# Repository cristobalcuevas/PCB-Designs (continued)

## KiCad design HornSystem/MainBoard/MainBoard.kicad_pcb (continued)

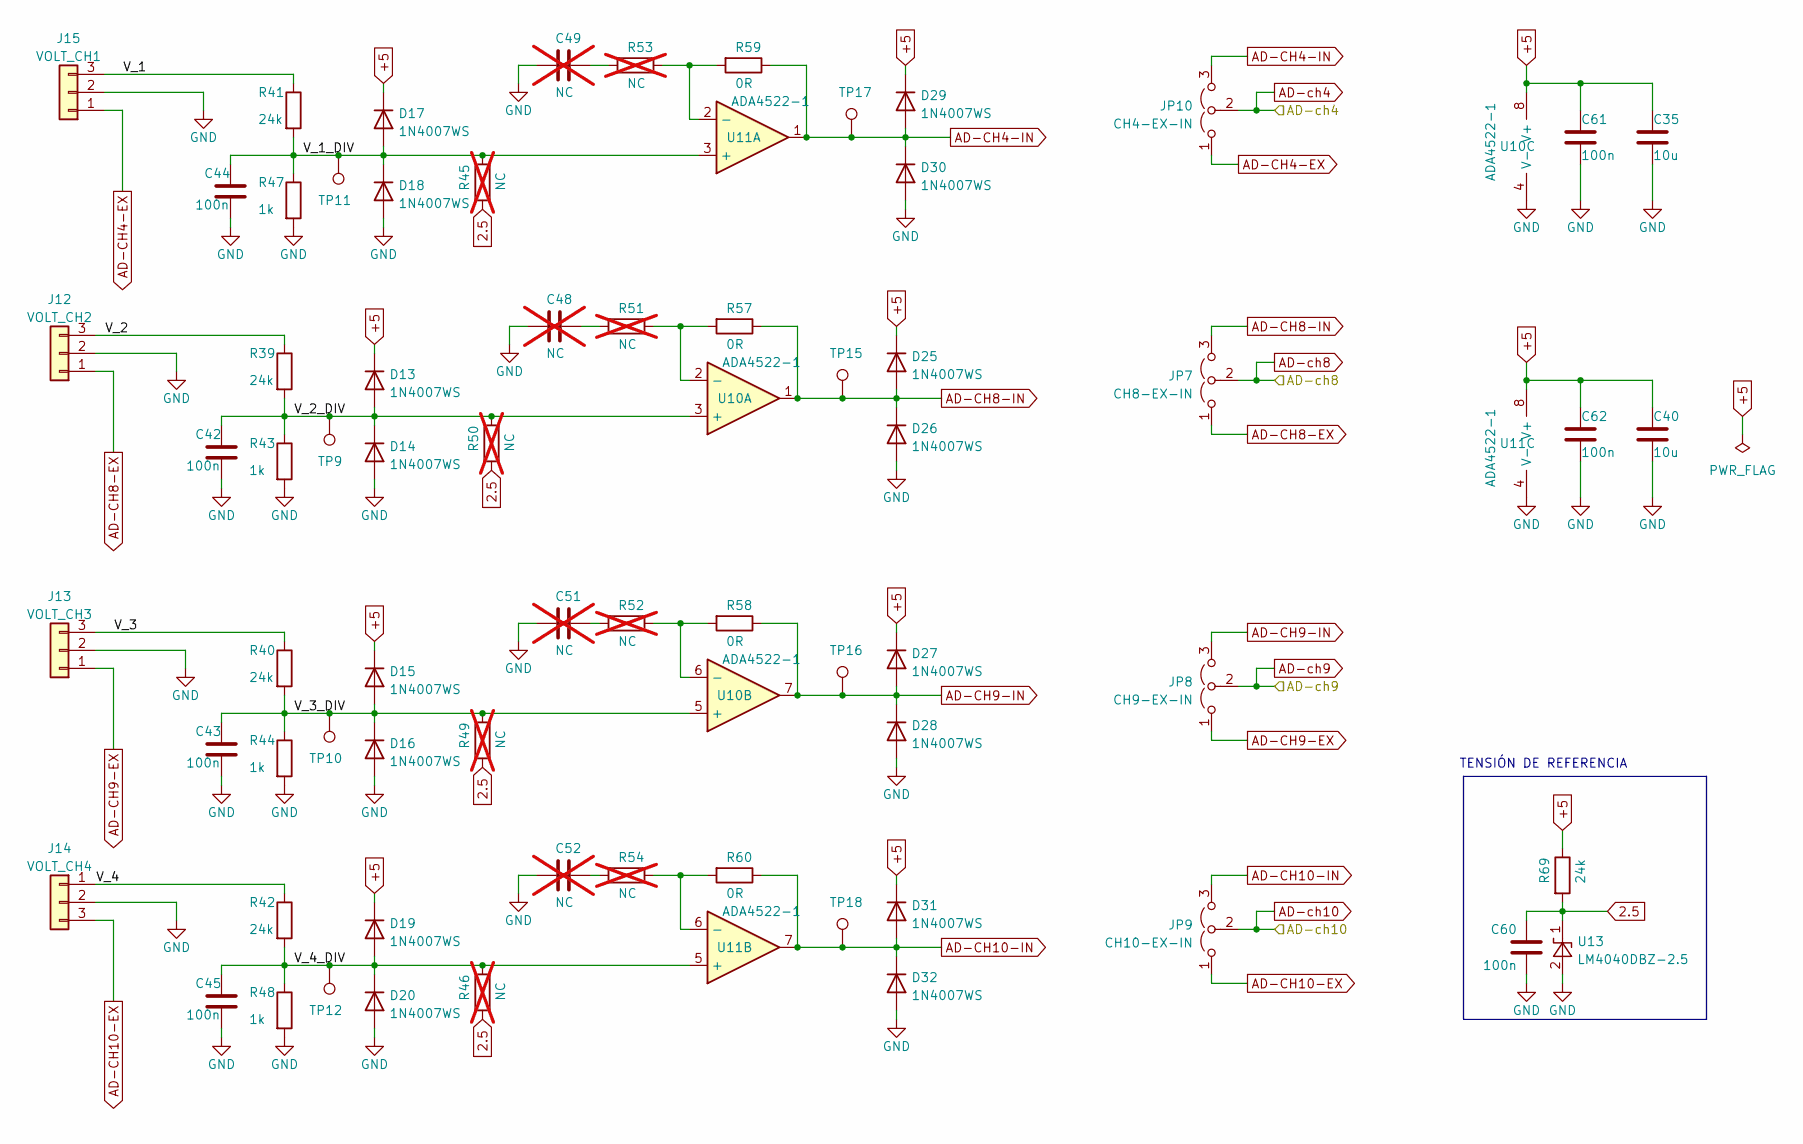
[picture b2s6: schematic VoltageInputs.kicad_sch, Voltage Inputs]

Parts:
C35, C40: 10u; C_0805_2012Metric; JLCPCB Part C380331
C42, C43, C44, C45, C60, C61, C62: 100n; C_0805_2012Metric; JLCPCB Part C710457
C48, C49, C51, C52: NC; C_0805_2012Metric; not fitted
D13, D14, D15, D16, D17, D18, D19, D20, D25, D26, D27, D28, D29, D30, D31, D32: 1N4007WS; D_SOD-323; JLCPCB Part C193404
J12: VOLT_CH2; PinHeader_1x03_P2.54mm_Vertical
J13: VOLT_CH3; PinHeader_1x03_P2.54mm_Vertical
J14: VOLT_CH4; PinHeader_1x03_P2.54mm_Vertical
J15: VOLT_CH1; PinHeader_1x03_P2.54mm_Vertical
JP7: CH8-EX-IN; SolderJumper-3_P1.3mm_Open_RoundedPad1.0x1.5mm_NumberLabels
JP8: CH9-EX-IN; SolderJumper-3_P1.3mm_Open_RoundedPad1.0x1.5mm_NumberLabels
JP9: CH10-EX-IN; SolderJumper-3_P1.3mm_Open_RoundedPad1.0x1.5mm_NumberLabels
JP10: CH4-EX-IN; SolderJumper-3_P1.3mm_Open_RoundedPad1.0x1.5mm_NumberLabels
R39, R40, R41, R42, R69: 24k; R_0805_2012Metric; JLCPCB Part C286604
R43, R44, R47, R48: 1k; R_0805_2012Metric; JLCPCB Part C335229
R45, R46, R49, R50, R51, R52, R53, R54: NC; R_0805_2012Metric; not fitted
R57, R58, R59, R60: 0R; R_0805_2012Metric; JLCPCB Part C2907288
TP9, TP10, TP11, TP12, TP15, TP16, TP17, TP18: TestPoint; TestPoint_Pad_D1.0mm
U10, U11: ADA4522-1; MSOP-8_3x3mm_P0.65mm; JLCPCB Part C127898
U13: LM4040DBZ-2.5; SOT-23; JLCPCB Part C131939

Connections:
2.5: C60.2, R45.2, R46.2, R49.2, R50.2, R69.2, U13.1 (K)
+5: C35.1, C40.1, C61.1, C62.1, D13.1 (K), D15.1 (K), D17.1 (K), D19.1 (K), D25.1 (K), D27.1 (K), D29.1 (K), D31.1 (K), R69.1, U10.8 (V+), U11.8 (V+); also elsewhere on the board
/VoltageInputs/V_1: J15.3, R41.1
/VoltageInputs/V_1_DIV: C44.1, D17.2 (A), D18.1 (K), R41.2, R45.1, R47.1, TP11.1, U11.3 (+)
/VoltageInputs/V_2: J12.3, R39.1
/VoltageInputs/V_2_DIV: C42.1, D13.2 (A), D14.1 (K), R39.2, R43.1, R50.1, TP9.1, U10.3 (+)
/VoltageInputs/V_3: J13.3, R40.1
/VoltageInputs/V_3_DIV: C43.1, D15.2 (A), D16.1 (K), R40.2, R44.1, R49.1, TP10.1, U10.5 (+)
/VoltageInputs/V_4: J14.1, R42.1
/VoltageInputs/V_4_DIV: C45.1, D19.2 (A), D20.1 (K), R42.2, R46.1, R48.1, TP12.1, U11.5 (+)
AD-CH4-EX: J15.1, JP10.1 (A)
AD-CH4-IN: D29.2 (A), D30.1 (K), JP10.3 (B), R59.1, TP17.1, U11.1
AD-CH8-EX: J12.1, JP7.1 (A)
AD-CH8-IN: D25.2 (A), D26.1 (K), JP7.3 (B), R57.1, TP15.1, U10.1
AD-CH9-EX: J13.1, JP8.1 (A)
AD-CH9-IN: D27.2 (A), D28.1 (K), JP8.3 (B), R58.1, TP16.1, U10.7
AD-CH10-EX: J14.3, JP9.1 (A)
AD-CH10-IN: D31.2 (A), D32.1 (K), JP9.3 (B), R60.1, TP18.1, U11.7
AD-ch4: JP10.2 (C); also elsewhere on the board
AD-ch8: JP7.2 (C); also elsewhere on the board
AD-ch9: JP8.2 (C); also elsewhere on the board
AD-ch10: JP9.2 (C); also elsewhere on the board
GND: C35.2, C40.2, C42.2, C43.2, C44.2, C45.2, C48.2, C49.2, C51.2, C52.2, C60.1, C61.2, C62.2, D14.2 (A), D16.2 (A), D18.2 (A), D20.2 (A), D26.2 (A), D28.2 (A), D30.2 (A), D32.2 (A), J12.2, J13.2, J14.2, J15.2, R43.2, R44.2, R47.2, R48.2, U10.4 (V-), U11.4 (V-), U13.2 (A); also elsewhere on the board
unnamed: C48.1, R51.2
unnamed: C49.1, R53.2
unnamed: C51.1, R52.2
unnamed: C52.1, R54.2
unnamed: R51.1, R57.2, U10.2 (-)
unnamed: R52.1, R58.2, U10.6 (-)
unnamed: R53.1, R59.2, U11.2 (-)
unnamed: R54.1, R60.2, U11.6 (-)

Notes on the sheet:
TENSIÓN DE REFERENCIA

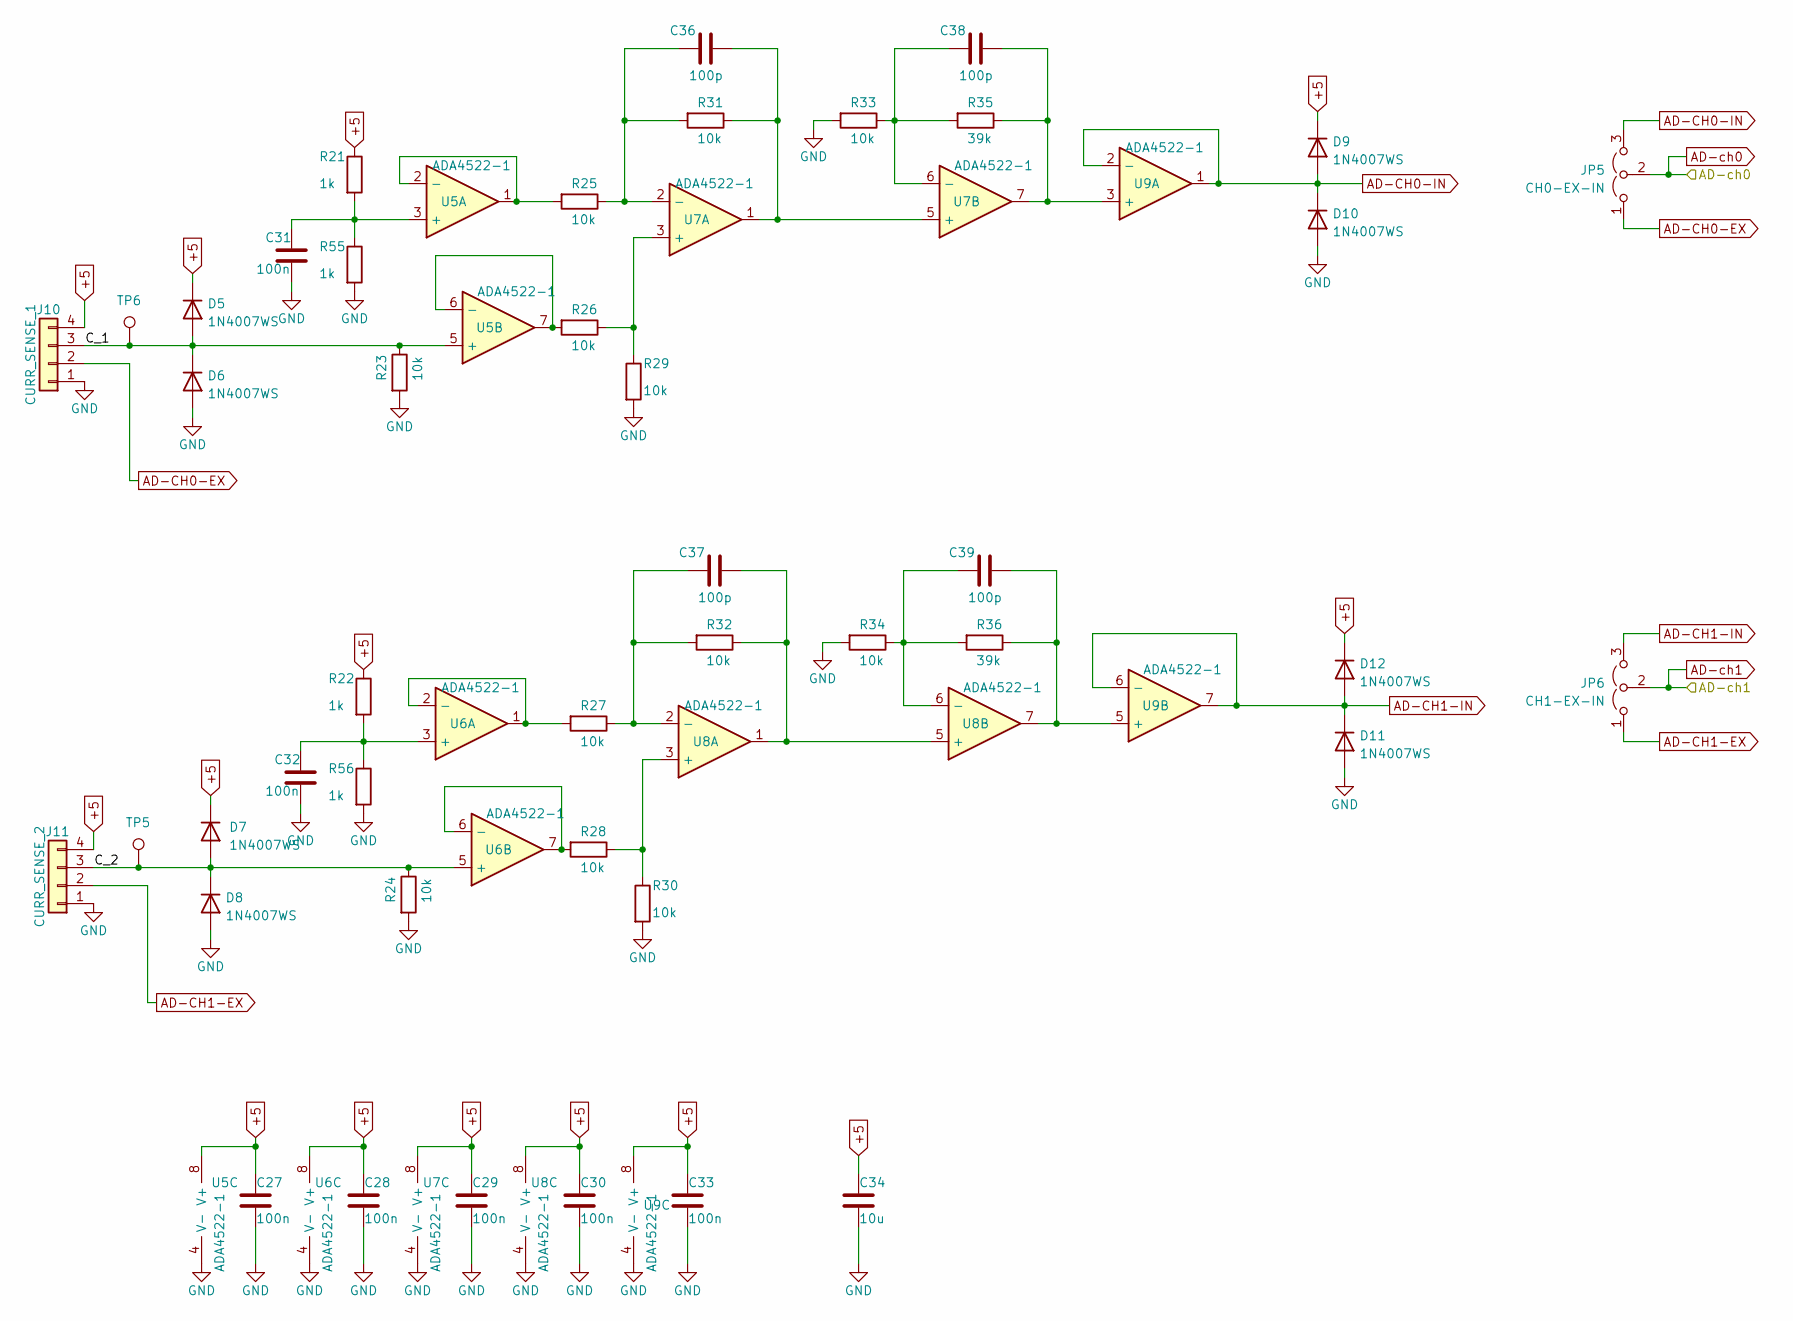
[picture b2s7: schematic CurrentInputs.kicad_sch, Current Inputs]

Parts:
C27, C28, C29, C30, C31, C32, C33: 100n; C_0805_2012Metric; JLCPCB Part C710457
C34: 10u; C_0805_2012Metric; JLCPCB Part C380331
C36, C37, C38, C39: 100p; C_0805_2012Metric; JLCPCB Part C2691714
D5, D6, D7, D8, D9, D10, D11, D12: 1N4007WS; D_SOD-323; JLCPCB Part C193404
J10: CURR_SENSE_1; PinHeader_1x04_P2.54mm_Vertical
J11: CURR_SENSE_2; PinHeader_1x04_P2.54mm_Vertical
JP5: CH0-EX-IN; SolderJumper-3_P1.3mm_Open_RoundedPad1.0x1.5mm_NumberLabels
JP6: CH1-EX-IN; SolderJumper-3_P1.3mm_Open_RoundedPad1.0x1.5mm_NumberLabels
R21, R22, R55, R56: 1k; R_0805_2012Metric; JLCPCB Part C335229
R23, R24, R25, R26, R27, R28, R29, R30, R31, R32, R33, R34: 10k; R_0805_2012Metric; JLCPCB Part C212284
R35, R36: 39k; R_0805_2012Metric; JLCPCB Part C139877
TP5, TP6: TestPoint; TestPoint_Pad_D1.0mm
U5, U6, U7, U8, U9: ADA4522-1; MSOP-8_3x3mm_P0.65mm; JLCPCB Part C127898

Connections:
+5: C27.1, C28.1, C29.1, C30.1, C33.1, C34.1, D5.1 (K), D7.1 (K), D9.1 (K), D12.1 (K), J10.4, J11.4, R21.1, R22.1, U5.8 (V+), U6.8 (V+), U7.8 (V+), U8.8 (V+), U9.8 (V+); also elsewhere on the board
/CurrentInputs/C_1: D5.2 (A), D6.1 (K), J10.3, R23.1, TP6.1, U5.5 (+)
/CurrentInputs/C_2: D7.2 (A), D8.1 (K), J11.3, R24.1, TP5.1, U6.5 (+)
AD-CH0-EX: J10.2, JP5.1 (A)
AD-CH0-IN: D9.2 (A), D10.1 (K), JP5.3 (B), U9.1, U9.2 (-)
AD-CH1-EX: J11.2, JP6.1 (A)
AD-CH1-IN: D11.1 (K), D12.2 (A), JP6.3 (B), U9.6 (-), U9.7
AD-ch0: JP5.2 (C); also elsewhere on the board
AD-ch1: JP6.2 (C); also elsewhere on the board
GND: C27.2, C28.2, C29.2, C30.2, C31.2, C32.2, C33.2, C34.2, D6.2 (A), D8.2 (A), D10.2 (A), D11.2 (A), J10.1, J11.1, R23.2, R24.2, R29.2, R30.2, R33.2, R34.2, R55.2, R56.2, U5.4 (V-), U6.4 (V-), U7.4 (V-), U8.4 (V-), U9.4 (V-); also elsewhere on the board
unnamed: C31.1, R21.2, R55.1, U5.3 (+)
unnamed: R25.2, U5.1, U5.2 (-)
unnamed: R26.2, U5.6 (-), U5.7
unnamed: C32.1, R22.2, R56.1, U6.3 (+)
unnamed: R27.2, U6.1, U6.2 (-)
unnamed: R28.2, U6.6 (-), U6.7
unnamed: R26.1, R29.1, U7.3 (+)
unnamed: C36.1, R25.1, R31.2, U7.2 (-)
unnamed: C36.2, R31.1, U7.1, U7.5 (+)
unnamed: C38.1, R33.1, R35.2, U7.6 (-)
unnamed: R28.1, R30.1, U8.3 (+)
unnamed: C37.1, R27.1, R32.2, U8.2 (-)
unnamed: C37.2, R32.1, U8.1, U8.5 (+)
unnamed: C39.1, R34.1, R36.2, U8.6 (-)
unnamed: C38.2, R35.1, U7.7, U9.3 (+)
unnamed: C39.2, R36.1, U8.7, U9.5 (+)

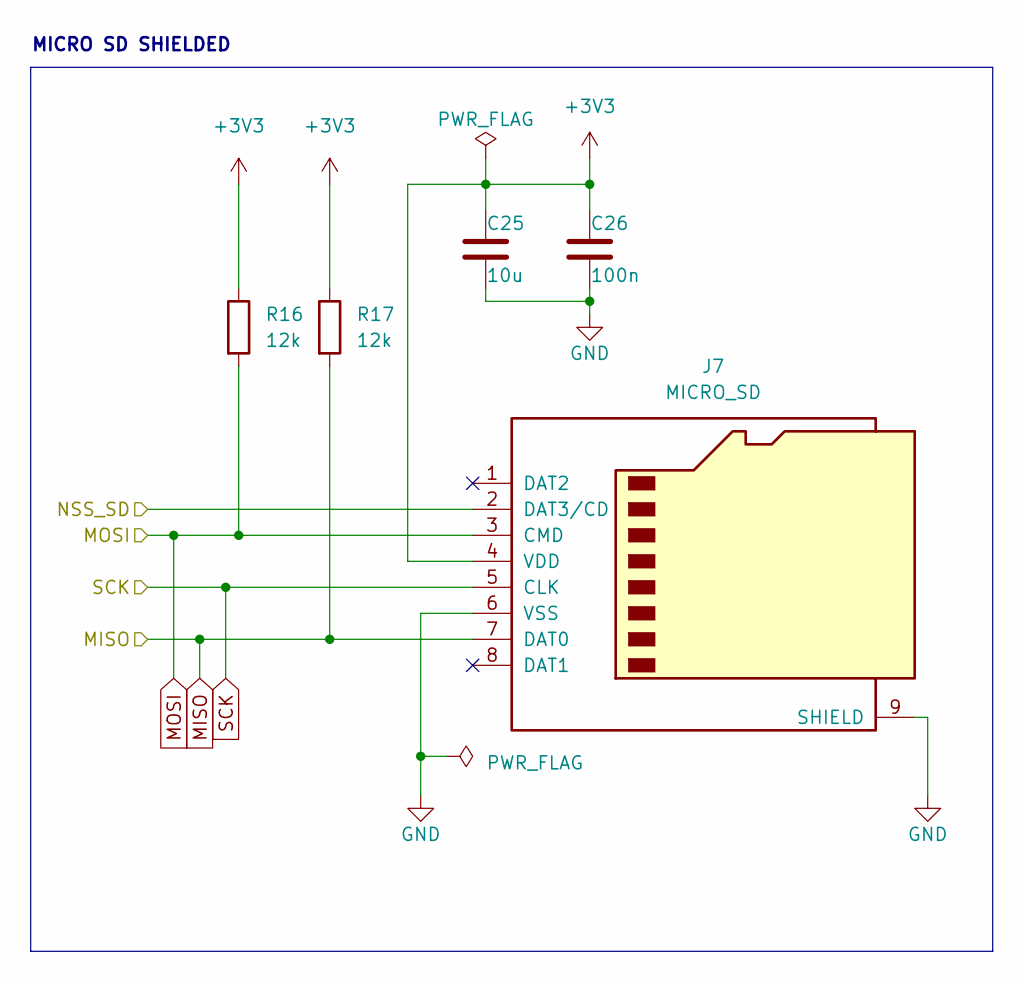
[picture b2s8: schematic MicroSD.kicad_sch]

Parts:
C25: 10u; C_0805_2012Metric; JLCPCB Part C380331
C26: 100n; C_0805_2012Metric; JLCPCB Part C710457
J7: MICRO_SD; microSD_HC_Molex_104031-0811; JLCPCB Part C585350
R16, R17: 12k; R_0805_2012Metric; JLCPCB Part C114556

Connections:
+3V3: C25.1, C26.1, J7.4 (VDD), R16.1, R17.1; also elsewhere on the board
/MCU/NSS_SD: J7.2 (DAT3/CD); also elsewhere on the board
GND: C25.2, C26.2, J7.6 (VSS), J7.9 (SHIELD); also elsewhere on the board
MISO: J7.7 (DAT0), R17.2; also elsewhere on the board
MOSI: J7.3 (CMD), R16.2; also elsewhere on the board
SCK: J7.5 (CLK); also elsewhere on the board

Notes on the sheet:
MICRO SD SHIELDED

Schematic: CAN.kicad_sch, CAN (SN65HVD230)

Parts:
C15: 100n; C_0805_2012Metric; JLCPCB Part C710457
J8: CAN_MODE; PinHeader_1x03_P2.54mm_Vertical
J20: CAN; PinHeader_1x02_P2.54mm_Vertical
R8: 20k; R_0805_2012Metric; JLCPCB Part C136576
R18: 0R; R_0805_2012Metric; JLCPCB Part C2907288
R19: 120R; R_0805_2012Metric; JLCPCB Part C912585
U12: SN65HVD230; SOIC-8_3.9x4.9mm_P1.27mm; JLCPCB Part C12084

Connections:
+3V3: C15.1, R18.2, U12.3 (VCC); also elsewhere on the board
/CAN/CAN_H: J20.1, R19.1, U12.7 (CANH)
/CAN/CAN_L: J20.2, R19.2, U12.6 (CANL)
/CAN/RS: J8.2, R8.1, U12.8 (Rs)
CAN_RX: U12.4 (R); also elsewhere on the board
CAN_TX: U12.1 (D); also elsewhere on the board
GND: C15.2, J8.3, R8.2, U12.2 (GND); also elsewhere on the board
unnamed: J8.1, R18.1

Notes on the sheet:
CAN

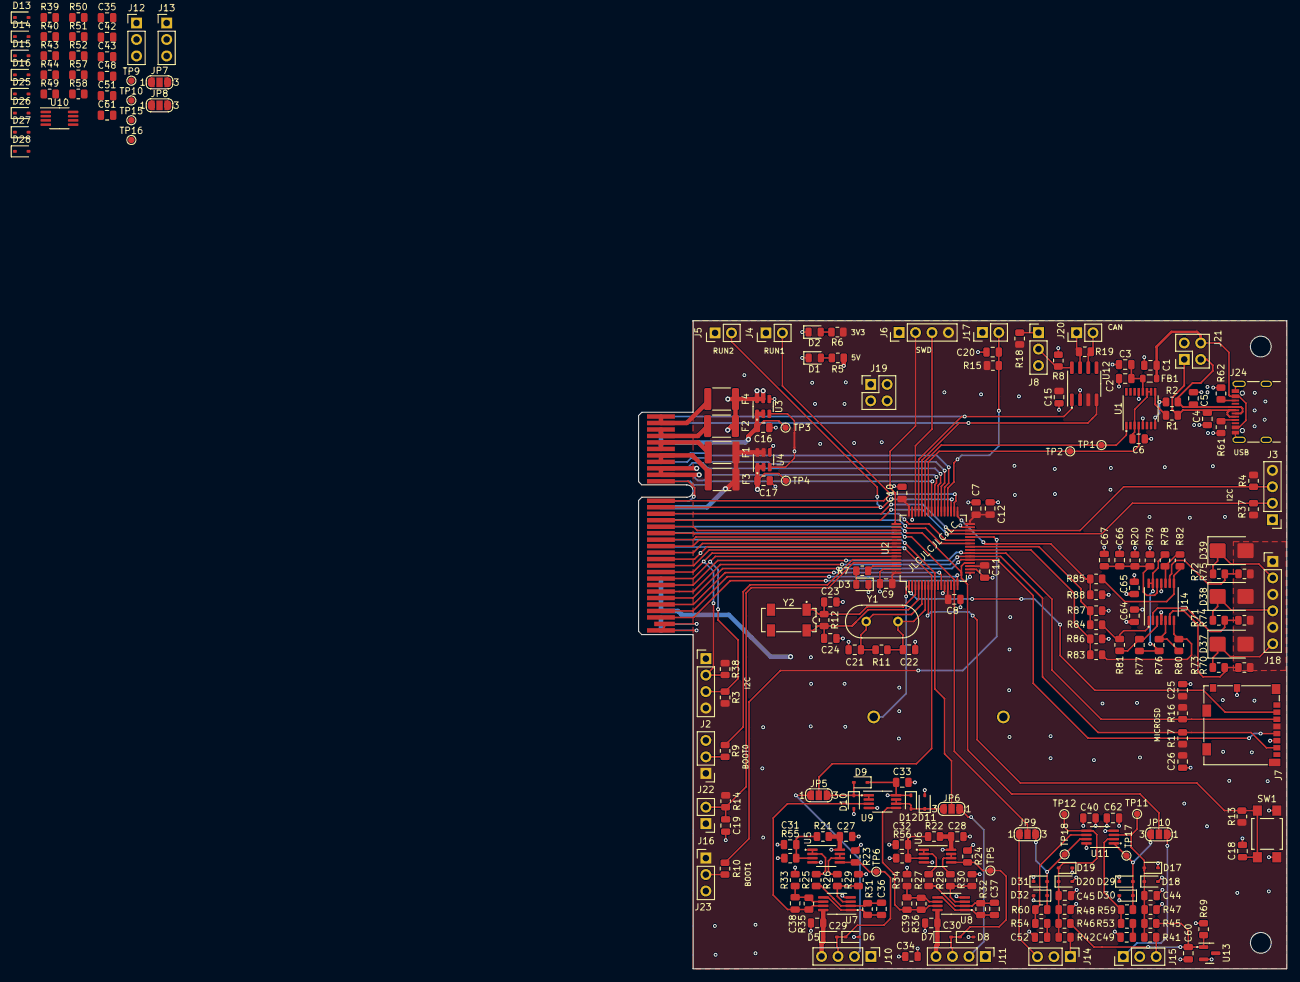
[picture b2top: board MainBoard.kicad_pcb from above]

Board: 4 copper layers, 100.0 x 100.0 mm, 233 parts (1 on the bottom side), 140 nets.

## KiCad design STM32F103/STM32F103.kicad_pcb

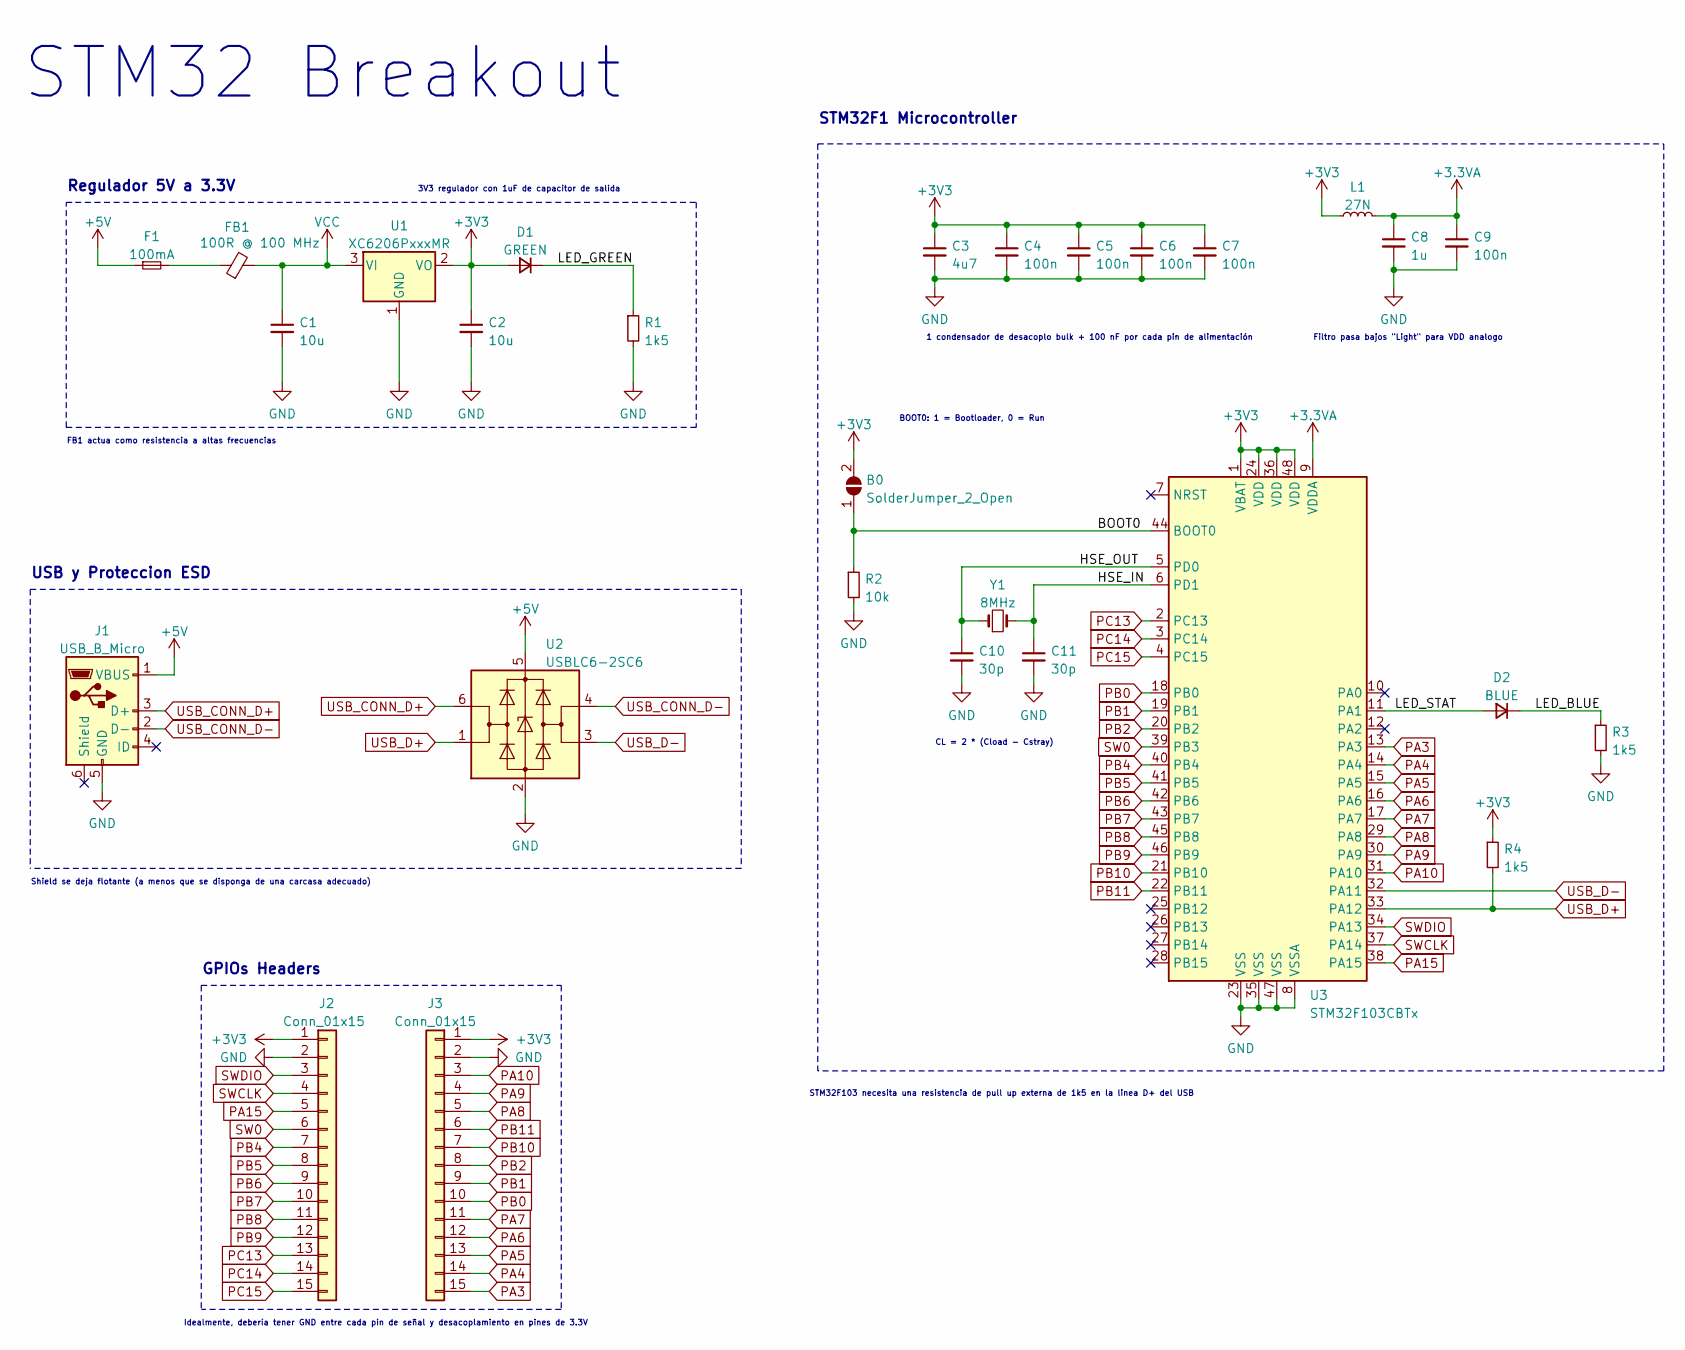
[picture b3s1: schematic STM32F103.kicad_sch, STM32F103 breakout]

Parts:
B0: SolderJumper_2_Open; SolderJumper-2_P1.3mm_Open_Pad1.0x1.5mm
C1, C2: 10u; C_0603_1608Metric
C3: 4u7; C_0603_1608Metric
C4, C5, C6, C7, C9: 100n; C_0402_1005Metric
C8: 1u; C_0402_1005Metric
C10, C11: 30p; C_0402_1005Metric
D1: GREEN; LED_0603_1608Metric
D2: BLUE; LED_0603_1608Metric
F1: 100mA; Fuse_0603_1608Metric
FB1: 100R @ 100 MHz; L_0805_2012Metric
J1: USB_B_Micro; USB_Micro-B_Wuerth_629105150521
J2, J3: Conn_01x15; PinHeader_1x15_P2.54mm_Vertical
L1: 27N; L_0402_1005Metric
R1, R3: 1k5; R_0603_1608Metric
R2: 10k; R_0402_1005Metric
R4: 1k5; R_0402_1005Metric
U1: XC6206PxxxMR; SOT-23
U2: USBLC6-2SC6; SOT-23-6
U3: STM32F103CBTx; LQFP-48_7x7mm_P0.5mm
Y1: 8MHz; Crystal_SMD_5032-2Pin_5.0x3.2mm

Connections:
+3.3VA: C8.1, C9.1, L1.2, U3.9 (VDDA)
+3V3: B0.2 (B), C2.1, C3.1, C4.1, C5.1, C6.1, C7.1, D1.2 (A), J2.1, J3.1, L1.1, R4.1, U1.2 (VO), U3.1 (VBAT), U3.24 (VDD), U3.36 (VDD), U3.48 (VDD)
+5V: F1.1, J1.1 (VBUS), U2.5 (VBUS)
/BOOT0: B0.1 (A), R2.1, U3.44 (BOOT0)
/HSE_IN: C11.1, U3.6 (PD1), Y1.2
/HSE_OUT: C10.1, U3.5 (PD0), Y1.1
/LED_BLUE: D2.1 (K), R3.1
/LED_GREEN: D1.1 (K), R1.1
/LED_STAT: D2.2 (A), U3.11 (PA1)
GND: C1.2, C2.2, C3.2, C4.2, C5.2, C6.2, C7.2, C8.2, C9.2, C10.2, C11.2, J1.5 (GND), J2.2, J3.2, R1.2, R2.2, R3.2, U1.1 (GND), U2.2 (GND), U3.8 (VSSA), U3.23 (VSS), U3.35 (VSS), U3.47 (VSS)
unnamed: F1.2, FB1.1
PA3: J3.15, U3.13 (PA3)
PA4: J3.14, U3.14 (PA4)
PA5: J3.13, U3.15 (PA5)
PA6: J3.12, U3.16 (PA6)
PA7: J3.11, U3.17 (PA7)
PA8: J3.5, U3.29 (PA8)
PA9: J3.4, U3.30 (PA9)
PA10: J3.3, U3.31 (PA10)
PA15: J2.5, U3.38 (PA15)
PB0: J3.10, U3.18 (PB0)
PB1: J3.9, U3.19 (PB1)
PB2: J3.8, U3.20 (PB2)
PB4: J2.7, U3.40 (PB4)
PB5: J2.8, U3.41 (PB5)
PB6: J2.9, U3.42 (PB6)
PB7: J2.10, U3.43 (PB7)
PB8: J2.11, U3.45 (PB8)
PB9: J2.12, U3.46 (PB9)
PB10: J3.7, U3.21 (PB10)
PB11: J3.6, U3.22 (PB11)
PC13: J2.13, U3.2 (PC13)
PC14: J2.14, U3.3 (PC14)
PC15: J2.15, U3.4 (PC15)
SW0: J2.6, U3.39 (PB3)
SWCLK: J2.4, U3.37 (PA14)
SWDIO: J2.3, U3.34 (PA13)
USB_CONN_D+: J1.3 (D+), U2.6 (I/O1)
USB_CONN_D-: J1.2 (D-), U2.4 (I/O2)
USB_D+: R4.2, U2.1 (I/O1), U3.33 (PA12)
USB_D-: U2.3 (I/O2), U3.32 (PA11)
VCC: C1.1, FB1.2, U1.3 (VI)

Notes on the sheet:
Regulador 5V a 3.3V
STM32F1 Microcontroller
STM32F103 necesita una resistencia de pull up externa de 1k5 en la linea D+ del USB
Filtro pasa bajos "Light" para VDD analogo
1 condensador de desacoplo bulk + 100 nF por cada pin de alimentación
FB1 actua como resistencia a altas frecuencias
CL = 2 * (Cload - Cstray)
Idealmente, debería tener GND entre cada pin de señal y desacoplamiento en pines de 3.3V
USB y Proteccion ESD
Shield se deja flotante (a menos que se disponga de una carcasa adecuado)
BOOT0: 1 = Bootloader, 0 = Run
STM32 Breakout
3V3 regulador con 1uF de capacitor de salida
GPIOs Headers

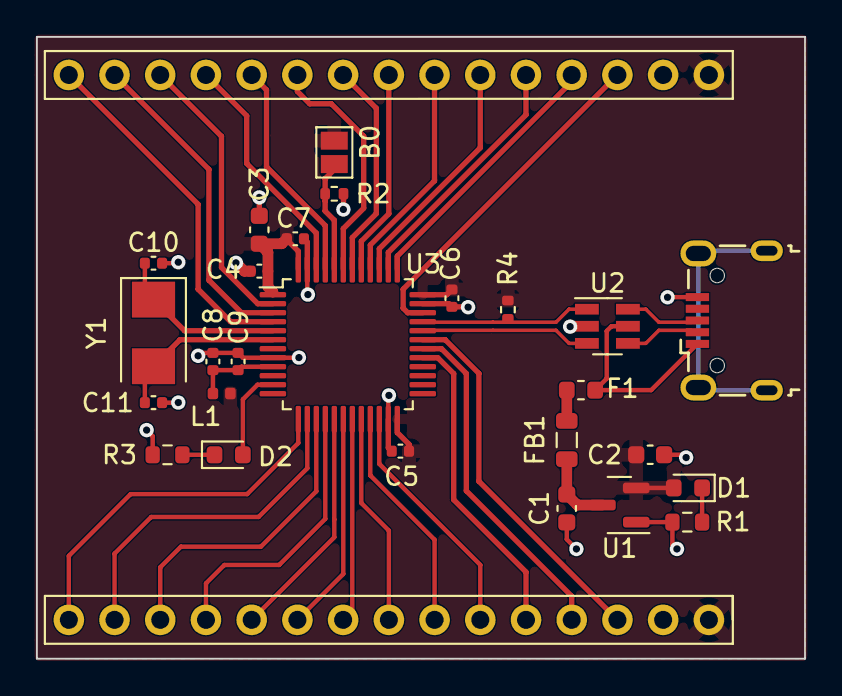
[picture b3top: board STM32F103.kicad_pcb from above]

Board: 2 copper layers, 42.7 x 34.5 mm, 28 parts (0 on the bottom side), 42 nets.

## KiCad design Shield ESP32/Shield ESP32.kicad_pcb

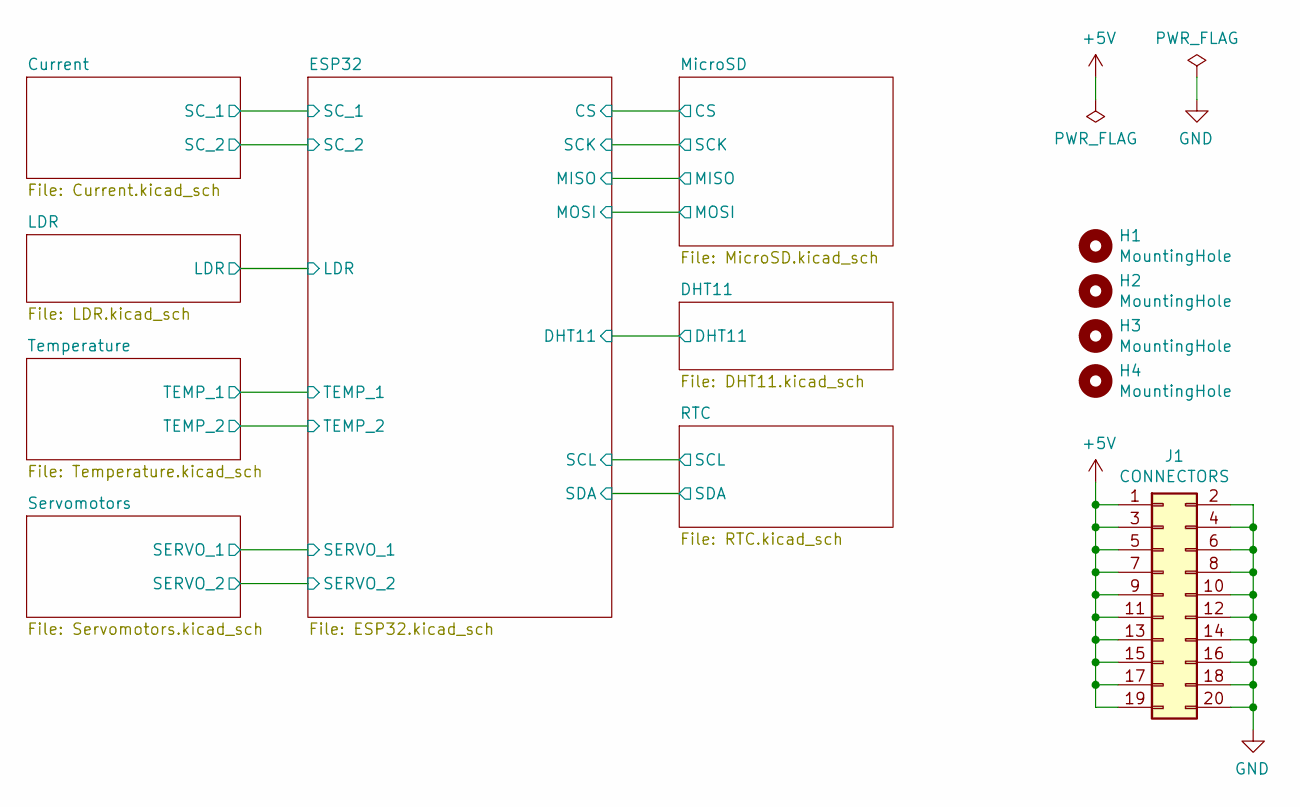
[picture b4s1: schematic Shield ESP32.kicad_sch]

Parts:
H1, H2, H3, H4: MountingHole; MountingHole_3.2mm_M3_ISO7380_Pad
J1: CONNECTORS; PinHeader_2x10_P2.54mm_Vertical; PartNumber 2011H-2X05G01SJ030B

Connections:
GND: J1.2, J1.4, J1.6, J1.8, J1.10, J1.12, J1.14, J1.16, J1.18, J1.20; also elsewhere on the board

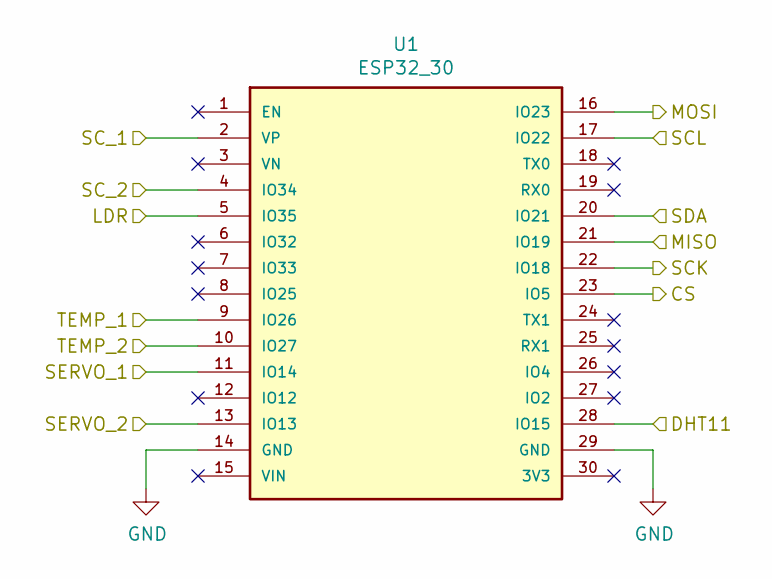
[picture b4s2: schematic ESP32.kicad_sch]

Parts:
U1: ESP32_30

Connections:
/Corriente/SC_1: U1.2 (VP); also elsewhere on the board
/Corriente/SC_2: U1.4 (IO34); also elsewhere on the board
/DHT11/DHT11: U1.28 (IO15); also elsewhere on the board
/ESP32/CS: U1.23 (IO5); also elsewhere on the board
/ESP32/LDR: U1.5 (IO35); also elsewhere on the board
/ESP32/MISO: U1.21 (IO19); also elsewhere on the board
/ESP32/MOSI: U1.16 (IO23); also elsewhere on the board
/ESP32/SCK: U1.22 (IO18); also elsewhere on the board
/ESP32/SCL: U1.17 (IO22); also elsewhere on the board
/ESP32/SDA: U1.20 (IO21); also elsewhere on the board
/ESP32/SERVO_1: U1.11 (IO14); also elsewhere on the board
/ESP32/SERVO_2: U1.13 (IO13); also elsewhere on the board
/ESP32/TEMP_1: U1.9 (IO26); also elsewhere on the board
/ESP32/TEMP_2: U1.10 (IO27); also elsewhere on the board
GND: U1.14 (GND), U1.29 (GND); also elsewhere on the board

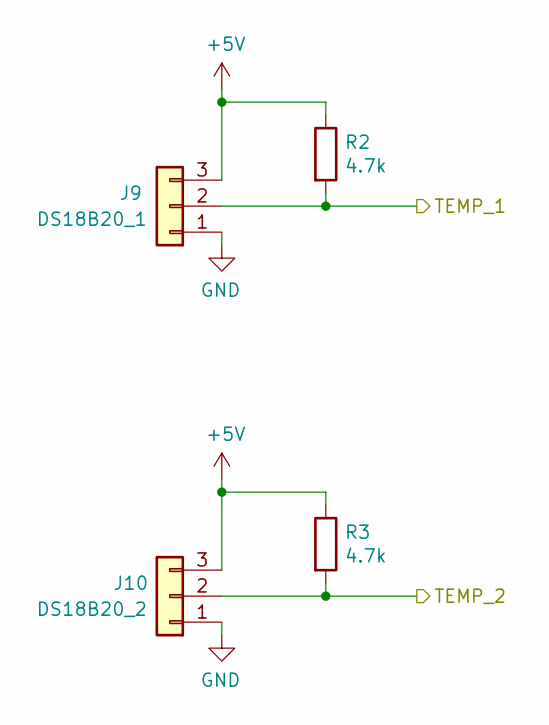
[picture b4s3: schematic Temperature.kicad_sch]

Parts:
J9: DS18B20_1; PinHeader_1x03_P2.54mm_Horizontal; PartNumber 2011-1X03G00SD025B
J10: DS18B20_2; PinHeader_1x03_P2.54mm_Horizontal; PartNumber 2011-1X03G00SD025B
R2, R3: 4.7k; R_Axial_DIN0207_L6.3mm_D2.5mm_P7.62mm_Horizontal

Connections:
/ESP32/TEMP_1: J9.2, R2.2; also elsewhere on the board
/ESP32/TEMP_2: J10.2, R3.2; also elsewhere on the board
GND: J9.1, J10.1; also elsewhere on the board

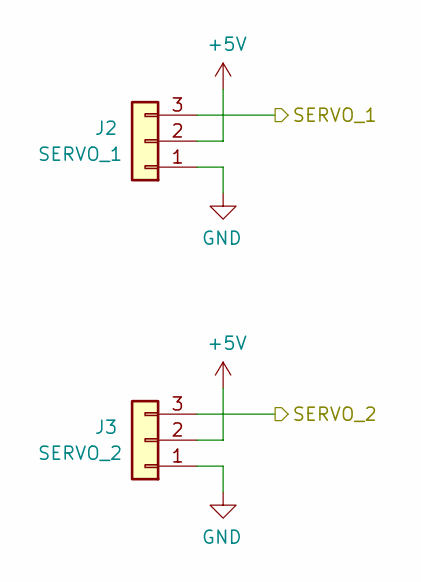
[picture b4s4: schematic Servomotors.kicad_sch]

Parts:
J2: SERVO_1; PinHeader_1x03_P2.54mm_Horizontal; PartNumber 2011-1X03G00SD025B
J3: SERVO_2; PinHeader_1x03_P2.54mm_Horizontal; PartNumber 2011-1X03G00SD025B

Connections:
/ESP32/SERVO_1: J2.3; also elsewhere on the board
/ESP32/SERVO_2: J3.3; also elsewhere on the board
GND: J2.1, J3.1; also elsewhere on the board

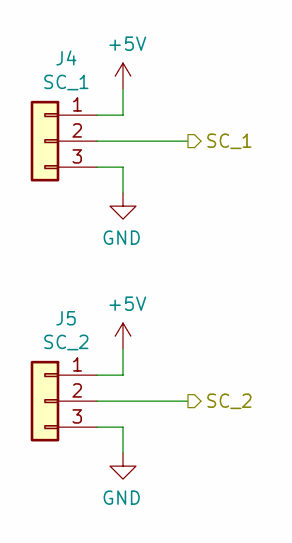
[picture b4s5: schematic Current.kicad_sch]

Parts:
J4: SC_1; PinHeader_1x03_P2.54mm_Horizontal; PartNumber 2011-1X03G00SD025B
J5: SC_2; PinHeader_1x03_P2.54mm_Horizontal; PartNumber 2011-1X03G00SD025B

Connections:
/Corriente/SC_1: J4.2; also elsewhere on the board
/Corriente/SC_2: J5.2; also elsewhere on the board
GND: J4.3, J5.3; also elsewhere on the board

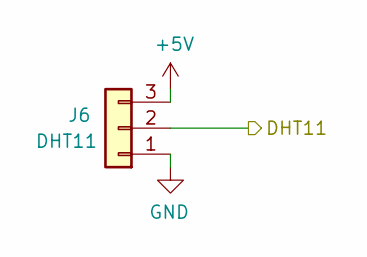
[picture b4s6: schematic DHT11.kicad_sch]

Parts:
J6: DHT11; PinHeader_1x03_P2.54mm_Horizontal; PartNumber 2011-1X03G00SD025B

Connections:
/DHT11/DHT11: J6.2; also elsewhere on the board
GND: J6.1; also elsewhere on the board

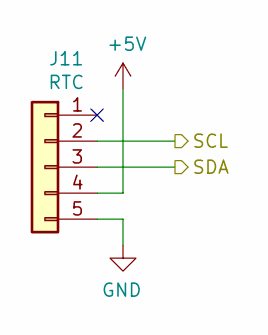
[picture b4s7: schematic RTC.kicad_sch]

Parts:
J11: RTC; PinHeader_1x05_P2.54mm_Horizontal; PartNumber 2111-1X05G00S-3.5-3.2B

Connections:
/ESP32/SCL: J11.2; also elsewhere on the board
/ESP32/SDA: J11.3; also elsewhere on the board
GND: J11.5; also elsewhere on the board

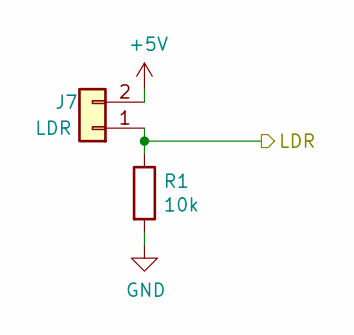
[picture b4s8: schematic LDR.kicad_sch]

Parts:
J7: LDR; PinHeader_1x02_P2.54mm_Horizontal; PartNumber 2111-1X02G00SB
R1: 10k; R_Axial_DIN0207_L6.3mm_D2.5mm_P7.62mm_Horizontal

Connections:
/ESP32/LDR: J7.1, R1.1; also elsewhere on the board
GND: R1.2; also elsewhere on the board

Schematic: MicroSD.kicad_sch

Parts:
J8: SD; PinHeader_1x06_P2.54mm_Horizontal; PartNumber 2011-1X06G00SI032B

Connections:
/ESP32/CS: J8.1; also elsewhere on the board
/ESP32/MISO: J8.3; also elsewhere on the board
/ESP32/MOSI: J8.4; also elsewhere on the board
/ESP32/SCK: J8.2; also elsewhere on the board
GND: J8.6; also elsewhere on the board

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
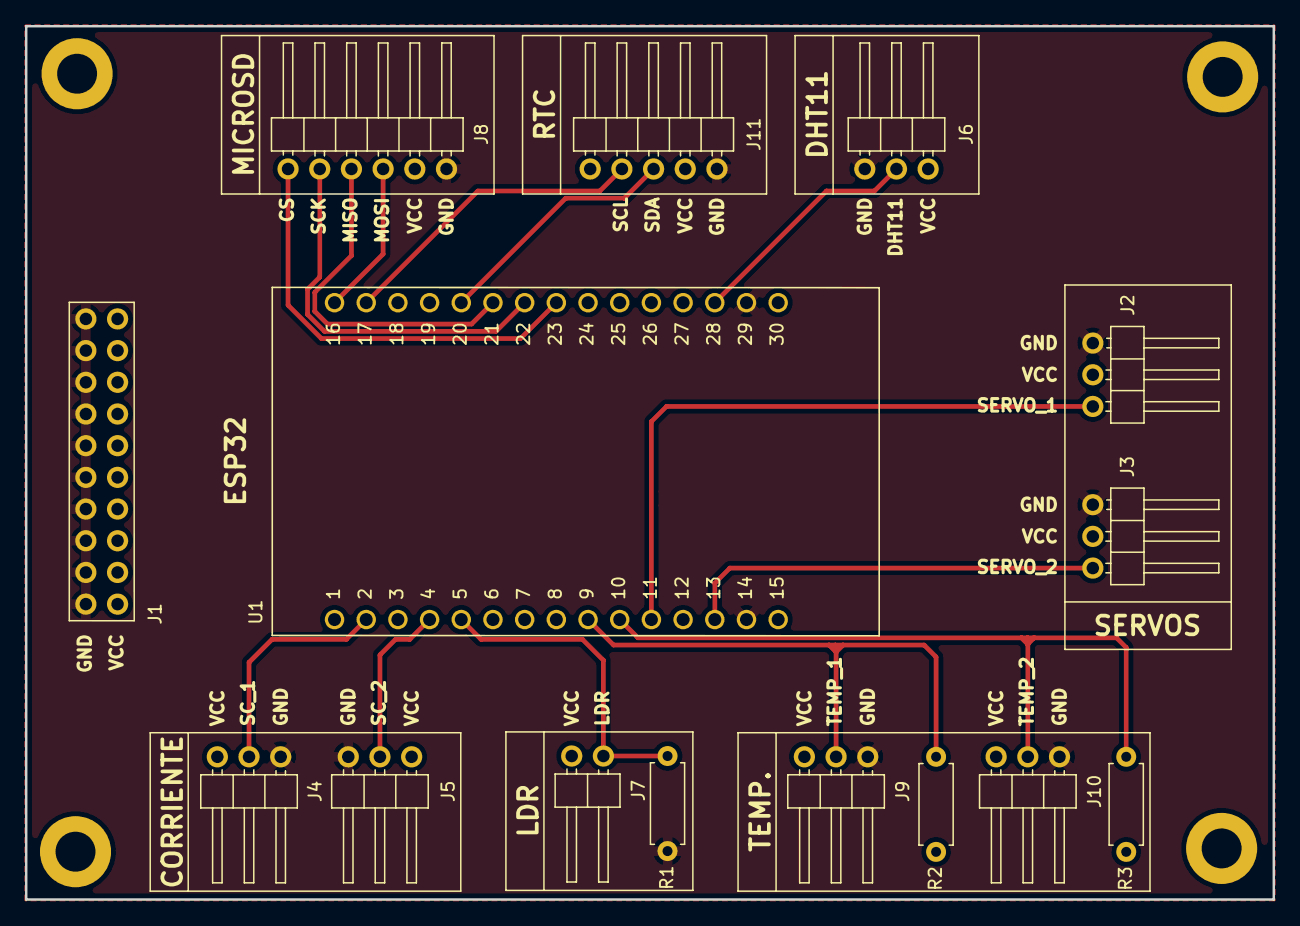
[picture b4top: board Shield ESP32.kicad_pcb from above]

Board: 2 copper layers, 100.0 x 70.0 mm, 19 parts (0 on the bottom side), 16 nets.

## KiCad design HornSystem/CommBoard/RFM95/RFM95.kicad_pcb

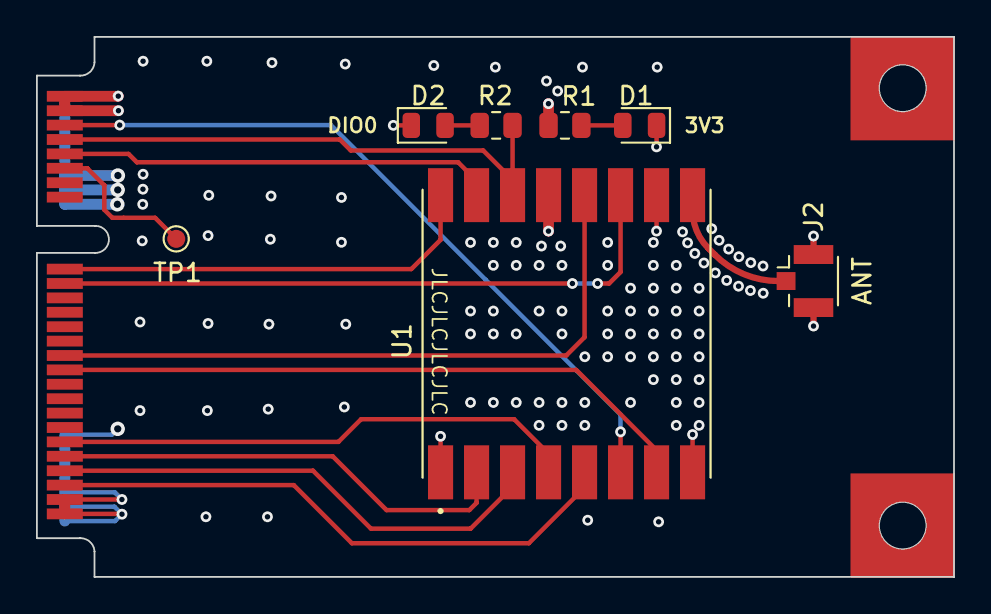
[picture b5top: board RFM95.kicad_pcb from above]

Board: 4 copper layers, 50.9 x 30.0 mm, 10 parts (0 on the bottom side), 17 nets.

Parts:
D1: LED 3V3; LED_0805_2012Metric
D2: LED DIO0; LED_0805_2012Metric
H1: H1; Pad_mini-PCIe
H2: H2; Pad_mini-PCIe
J1: Mini_PCI_Express; mini-PCIe_Connector
J2: UFL; U.FL_Hirose_U.FL-R-SMT-1_Vertical
R1, R2: 1k; R_0805_2012Metric
TP1: RXTX_RF; TestPoint_Pad_D1.0mm
U1: RFM95

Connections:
+3V3: J1.1, J1.2, J1.3, J1.4, J1.6, J1.8, J1.10, J1.12, J1.14, J1.16, R1.1, U1.13 (3.3V)
/Schematic/ANT: J2.1 (In), U1.9 (ANT)
/Schematic/LED_3V3: D1.2 (A), R1.2
/Schematic/LED_DIO0: D2.2 (A), R2.2
DIO0: J1.7, R2.1, U1.14 (DIO0)
DIO1: J1.9, U1.15 (DIO1)
DIO2: J1.17, U1.16 (DIO2)
DIO3: J1.19, U1.11 (DIO3)
DIO4: J1.29, U1.12 (DIO4)
DIO5: J1.31, U1.7 (DIO5)
GND: D1.1 (K), D2.1 (K), J1.40, J1.42, J1.44, J1.46, J1.48, J1.49, J1.50, J1.51, J1.52, J2.2 (Ext), U1.1 (GND), U1.8 (GND), U1.10 (GND)
MISO: J1.43, U1.2 (MISO)
MOSI: J1.45, U1.3 (MOSI)
NSS_LoRa: J1.47, U1.5 (NSS)
RST_LoRa: J1.5, U1.6 (RESET)
RXTX_RF: J1.11, TP1.1
SCK: J1.41, U1.4 (SCK)
